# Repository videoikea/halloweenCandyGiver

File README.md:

This is the CAD, budget, schematics, and any other additional files for a 6-DOF robot arm that looks for and picks up specific candy types in a Halloween candy bowl corresponding to user input.
I made this project both as part of Hack Club Stasis and as a personal passion project. First, it would be sick if kids rang the doorbell on Halloween and a robotic arm gave the candy to them instead of an actual person. Also, even when it fully functions in giving candy, I can repurpose to do other things, like stack objects, draw patterns onto paper, and more. Hack Club will give me both the money to build this project and Open Sauce tickets when it is finished.

Schematic:

PCB:

Full 3D Model:

Budget:
|Name               |Purpose                                                                                                    |Quantity|Total Cost (USD)|Link                                                                                                                                                                                                                                                                                                                                                                                                                                                                                                      |Distributor|
|-------------------|-----------------------------------------------------------------------------------------------------------|--------|----------------|----------------------------------------------------------------------------------------------------------------------------------------------------------------------------------------------------------------------------------------------------------------------------------------------------------------------------------------------------------------------------------------------------------------------------------------------------------------------------------------------------------|-----------|
|Raspberry Pi       |Inputs camera and button data and outputs servo positions                                                  |1       |40              |https://www.digikey.com/en/products/detail/raspberry-pi/SC0073/8571724                                                                                                                                                                                                                                                                                                                                                                                                                                    |Digikey    |
|Terminal Block     |Connects 14AWG wire to power supply and servo drivers                                                      |3       |0.96            |https://www.digikey.com/en/products/detail/same-sky-formerly-cui-devices/TB002-500-02BE/10064069                                                                                                                                                                                                                                                                                                                                                                                                          |Digikey    |
|Header Row (F)     |Structural and electrical support between PCB and Raspberry Pi                                             |2       |3.52            |https://www.digikey.com/en/products/detail/w%C3%BCrth-elektronik/61304021821/16608657                                                                                                                                                                                                                                                                                                                                                                                                                     |Digikey    |
|Push Button        |User presses a button that corresponds to a type of candy                                                  |4       |0.4             |https://www.digikey.com/en/products/detail/same-sky-formerly-cui-devices-/TS02-66-55-BK-160-LCR-D/15634374?gclsrc=aw.ds&gad_source=1&gad_campaignid=20243136172&gbraid=0AAAAADrbLlhl8y2A1lkF4FOXo2CeveWf1&gclid=Cj0KCQjwmunNBhDbARIsAOndKpn9HLTVNnSi38URbq4MfKIhHEw79Qnhzsc2nthJDEQcYhQfrIrBviAaApRQEALw_wcB                                                                                                                                                                                              |Digikey    |
|PCB                |Connects power supply to Raspberry Pi and servo drivers, connects Raspberry Pi to servo drivers and buttons|1       |12.81           |https://www.pcbway.com/Order/QuickOrderOnline                                                                                                                                                                                                                                                                                                                                                                                                                                                             |PCBWay     |
|Servo (6-pack)     |Converts PWM signal into positional radial motion                                                          |1       |26.98           |https://www.amazon.com/Deegoo-FPV-Servo-MG995-Metal-Gear/dp/B0D7M4LHBP/                                                                                                                                                                                                                                                                                                                                                                                                                                   |Amazon     |
|Camera             |Captures candy bowl and identifies different candy types                                                   |1       |6.99            |https://www.amazon.com/Arducam-Megapixels-Sensor-OV5647-Raspberry/dp/B012V1HEP4/                                                                                                                                                                                                                                                                                                                                                                                                                          |Amazon     |
|Shafts (8-pack)    |Structurally strong rod that provides an axis for rotation                                                 |1       |9.88            |https://www.amazon.com/Linear-Motion-Printer-Machine-Diameter/dp/B0BJD83HMG/                                                                                                                                                                                                                                                                                                                                                                                                                              |Amazon     |
|Bearings (20-pack) |Allows for fluid motion between shafts and 3D prints                                                       |        |5.99            |https://www.amazon.com/PCS-608-ZZ-Ball-Bearings/dp/B07CVBSC9Y/                                                                                                                                                                                                                                                                                                                                                                                                                                            |Amazon     |
|M4 Screws          |Screws for structural parts like plates and servos                                                         |1       |6.99            |https://www.amazon.com/Mr-Pieces-Button-Socket-Washers/dp/B0D6LLHBFY/                                                                                                                                                                                                                                                                                                                                                                                                                                     |Amazon     |
|M2.5 Screws        |Screws for electronics like camera and Raspberry Pi                                                        |1       |6.58            |https://www.amazon.com/Washers-Stainless-Machine-Assortment-Threaded/dp/B0DCKC41W3/                                                                                                                                                                                                                                                                                                                                                                                                                       |Amazon     |
|Filament           |Material that 3D printer turns into custom parts                                                           |1       |9.99            |https://www.amazon.com/Filament-Dimensional-Accuracy-Toughness-Resistance/dp/B0DS4BB39T/ref=sr_1_8?crid=19DLMZOHH39EI&dib=eyJ2IjoiMSJ9.yf4QrGfdb01bS0owhB7XaAL1s4Md4ktQ1OtfD_hfl9mzCbgWQGh0bwU--PiDLr19jmGkafGg-PXGoxMdLZmjfmRx6bRysu2pwbuB1wMxR8Pe9938Eem0e6ZQGu3ju7v4tUeKPaD_j1XNaczB3vYOVv-YUplmZQJxHHIIHY3mKbyeXddKMPOCO6FgCWfNdmwsxGOu4R5ln_1ctcdTKL9sJtyPwgvHh2hXQYV1Df0t89k.0O7UpoWXlGtNzHexIQWnEvsx7JbM3ywq2BVs-7tF3_s&dib_tag=se&keywords=petg&qid=1774128995&sprefix=pet%2Caps%2C185&sr=8-8&th=1|Amazon     |
|14AWG Wire         |Runs power between power supply, PCB, and controllers                                                      |1       |6.49            |https://www.amazon.com/HiFind-Electrical-Extension-Flexible-Lighting/dp/B0D922D4YF/                                                                                                                                                                                                                                                                                                                                                                                                                       |Amazon     |
|I2C to PWM (2-pack)|Converts Raspberry Pi I2C to servo PWM                                                                     |1       |8.99            |https://www.amazon.com/Dorhea-PCA9685-Interface-Controller-Raspberry/dp/B07RMTN4NZ                                                                                                                                                                                                                                                                                                                                                                                                                        |Amazon     |
|Power Supply       |Provides 5V15A power for circuit                                                                           |1       |19.99           |https://www.amazon.com/ALITOVE-Transformer-Adapter-Converter-Charger/dp/B06XK2DDW4/                                                                                                                                                                                                                                                                                                                                                                                                                       |Amazon     |
|Wall Outlet        |Converts wall power to supply's screw terminals                                                            |1       |11.99           |https://www.amazon.com/Vockjour-Appliance-Replacement-Pigtail-Listed/dp/B0FFB125CG/                                                                                                                                                                                                                                                                                                                                                                                                                       |Amazon     |
|PWM Extension      |Extends servo wires to controller                                                                          |1       |4.99            |https://www.amazon.com/VIMVIP-Female-Futaba-Extension-Control/dp/B00N8P8TT8/                                                                                                                                                                                                                                                                                                                                                                                                                              |Amazon     |

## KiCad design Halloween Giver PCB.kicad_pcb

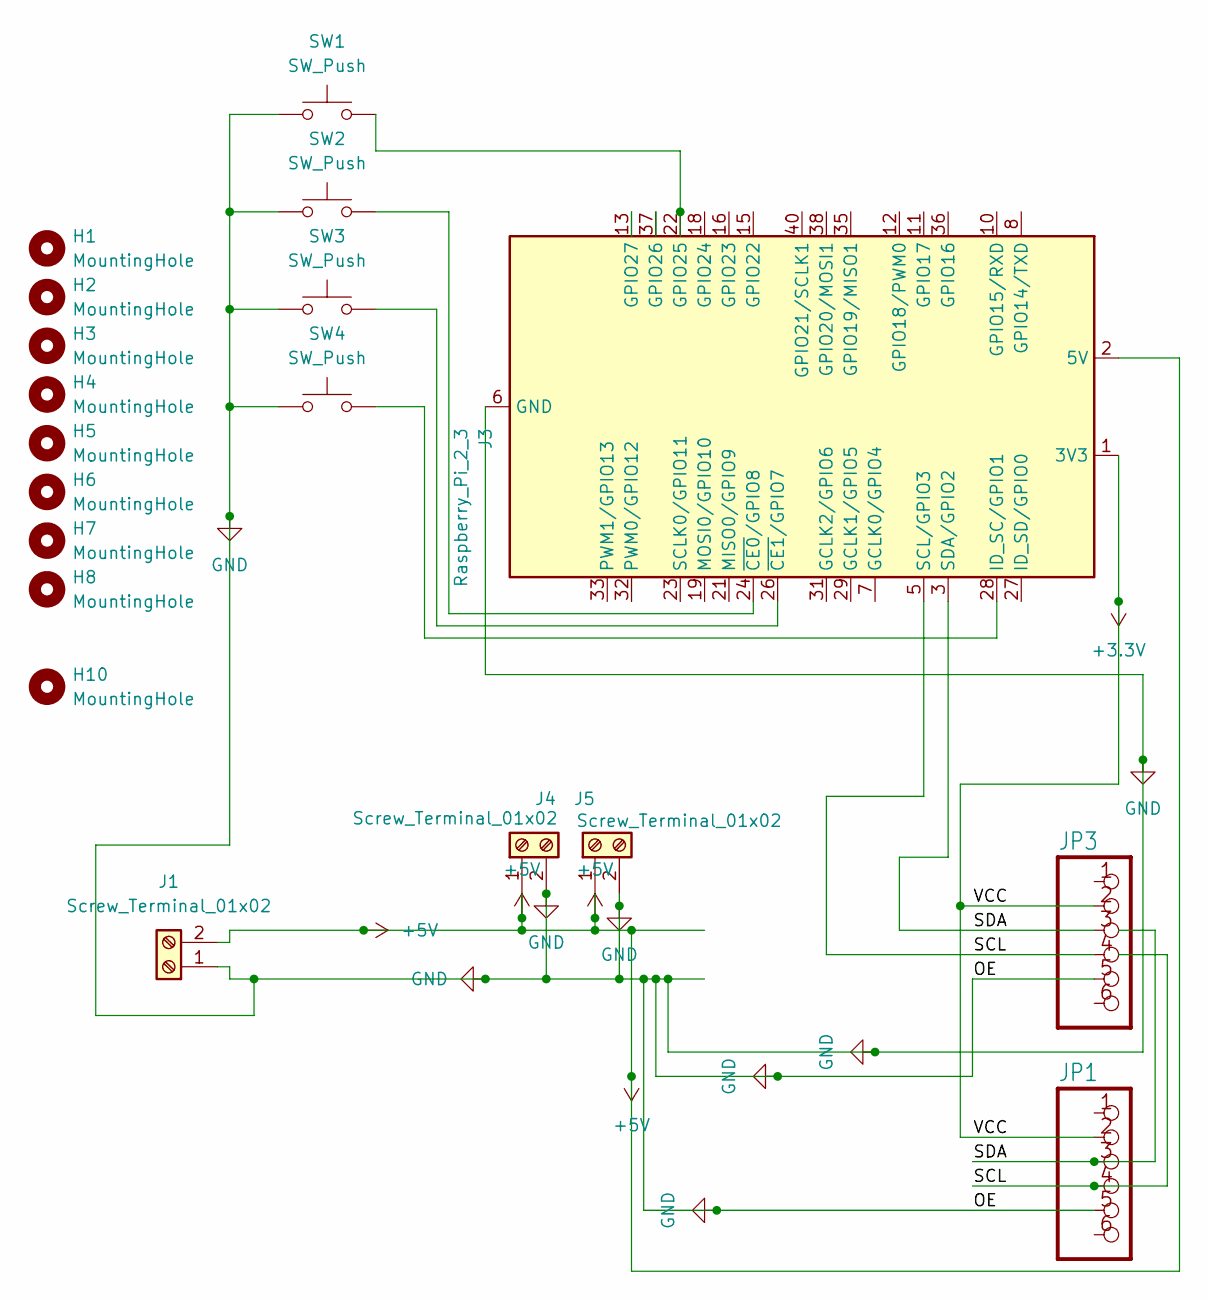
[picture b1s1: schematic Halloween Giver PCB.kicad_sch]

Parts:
H1, H2, H3, H4, H5, H6, H7, H8, H10: MountingHole; MountingHole_2.5mm
J1, J4, J5: Screw_Terminal_01x02; TerminalBlock_MaiXu_MX126-5.0-02P_1x02_P5.00mm
J3: Raspberry_Pi_2_3; PinSocket_2x20_P2.54mm_Vertical
JP1, JP3: PINHD-1X6CB; PinHeader_1x06_P2.54mm_Vertical
SW1, SW2, SW3, SW4: SW_Push; SW_PUSH_6mm

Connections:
+3.3V: J3.1 (3V3), J3.17 (3V3), JP1.2, JP3.2
+5V: J1.2, J3.2 (5V), J3.4 (5V), J4.1, J5.1
/SCL: J3.5 (SCL/GPIO3), JP1.4, JP3.4
/SDA: J3.3 (SDA/GPIO2), JP1.3, JP3.3
GND: J1.1, J3.6 (GND), J3.9 (GND), J3.14 (GND), J3.20 (GND), J3.25 (GND), J3.30 (GND), J3.34 (GND), J3.39 (GND), J4.2, J5.2, JP1.5, JP3.5, SW1.1, SW2.1, SW3.1, SW4.1
unnamed: J3.22 (GPIO25), SW1.2
unnamed: J3.28 (ID_SC/GPIO1), SW4.2
unnamed: J3.24 (~CE0/GPIO8), SW2.2
unnamed: J3.26 (~CE1/GPIO7), SW3.2

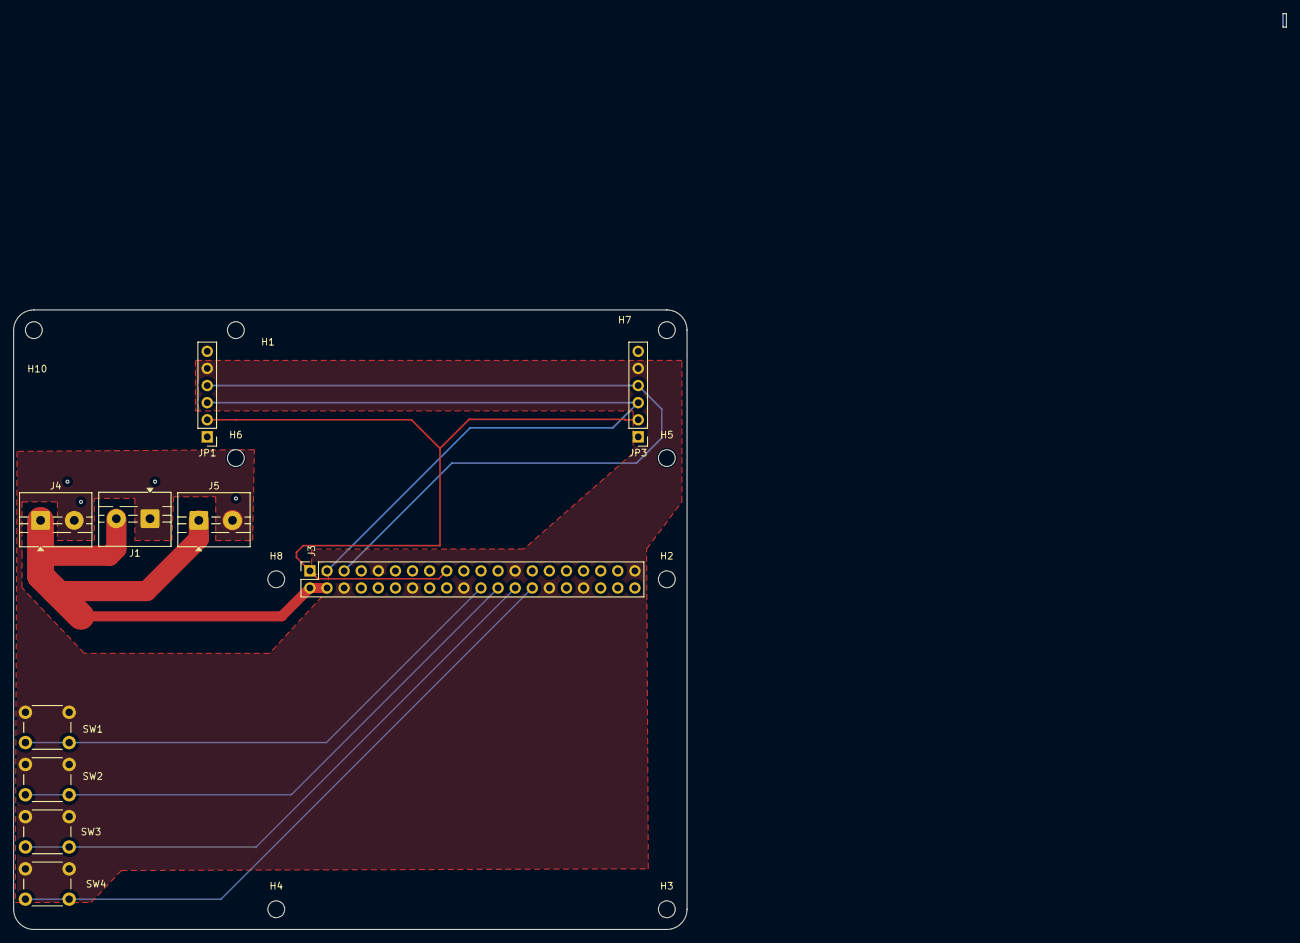
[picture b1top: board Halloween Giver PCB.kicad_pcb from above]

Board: 2 copper layers, 100.0 x 92.0 mm, 19 parts (0 on the bottom side), 9 nets.

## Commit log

2026-04-02 Add project description for 6-DOF robot arm
2026-04-02 Enhance README with project details and budget
    Added detailed project description, schematics, budget, and links to components for the 6-DOF robot arm.
2026-04-02 Rename Full.step to CAD Model.step
2026-04-02 Rename Halloween Candy Giver Budget - Sheet1.csv to Budget.csv
2026-04-02 Rename Halloween Candy Giver V2 PCB Files.zip to PCB Files.zip
2026-04-02 Rename PCB Files.zip to Gerber Files.zip
2026-04-02 Add STEP Full CAD model
2026-04-02 Rename Full.x_t to Parasolid Full CAD
2026-04-02 Rename Parasolid Full CAD to Parasolid Full CAD.x_t
2026-04-02 Rename STEP Full CAD to STEP Full CAD.step
2026-04-02 Rename Halloween Giver PCB.kicad_sch to electrical/Halloween Giver PCB.kicad_sch
2026-04-02 Rename Halloween Giver PCB.kicad_pro to electrical/Halloween Giver PCB.kicad_pro
2026-04-02 Rename Halloween Giver PCB.kicad_pcb to images/Halloween Giver PCB.kicad_pcb
2026-04-02 Rename Halloween Giver PCB.kicad_pcb to Halloween Giver PCB.kicad_pcb
2026-04-02 Rename Gerber Files.zip to electrical/Gerber Files.zip
2026-04-02 Rename Parasolid Full CAD.x_t to design/Parasolid Full CAD.x_t
2026-04-02 Rename STEP Full CAD.step to design/STEP Full CAD.step
2026-04-02 Rename Halloween Candy Giver V3 PCB Files.zip to electrical/Halloween Candy Giver V3 PCB Files.zip
2026-04-02 Rename Halloween Giver PCB.kicad_pcb to electrical/Halloween Giver PCB.kicad_pcb
